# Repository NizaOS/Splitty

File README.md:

<header style="text-align: center; margin-bottom: 40px;">
<h1 style="font-size: 3em; margin-bottom: 10px;">SPLITTY</h1>
<p style="font-size: 1.2em; color: #555;">A 40% Wireless Split Mechanical Keyboard</p>
<p><b>Low Profile &bull; Choc v1 &bull; ZMK Firmware &bull; 1000mAh Battery Life</b></p>
<hr>
</header>
<section>
<h2>Project Overview</h2>
<p>SPLITTY is a custom-built, wireless split keyboard designed for portability and ergonomics. It utilizes the <b>Seeed Studio XIAO nRF52840</b> for Bluetooth 5.0 connectivity and is built on a custom PCB optimized for <b>Kailh Choc v1</b> low-profile switches.</p>

<h3>why i made this project</h3>
    <p>i wanted a low profile split keyboard that was actually portable and didnt cost a fortune. most commerical options are too bulky or wired only so i decided to desin something that fits in a laptop bag easily while keeping the ergonomics of a split layout.</p>

<h3>how to use</h3>
    <p>to use the keyboard you need to flash zmk firmware to both halves. double tap reset button on the xiao to enter bootloader mode then drag and drop the uf2 files. once its flashed you can pair it to your computer via bluetooth settings by searching for splitty. the left side is usually the central half that connects to the pc.</p>
    <h3>Technical Specifications</h3>
    <ul>
        <li><b>Microcontroller:</b> 2x Seeed Studio XIAO nRF52840 (Bluetooth 5.0)</li>
        <li><b>Switch Type:</b> Kailh Choc v1 (PG1350) - Linear/Tactile/Clicky</li>
        <li><b>Battery:</b> 2x 1000mAh LiPo (WLY394058) - Approx. 1+ month battery life</li>
        <li><b>PCB Features:</b> Hotswap support, reversible footprint, 1.2mm thickness</li>
        <li><b>Firmware:</b> ZMK (Wireless-first firmware)</li>
    </ul>
</section>
<hr>
<section>
    <h2>Bill of Materials (BOM)</h2>
    <p><i>Prices estimated in USD based on INR conversion ($1 &#8776; &#8377;90.27).</i></p>
            <table border="1" cellpadding="10" cellspacing="0" style="width: 100%; border-collapse: collapse; text-align: left;">
        <thead>
            <tr style="background-color: #f2f2f2;">
                <th>Component</th>
                <th>Qty</th>
                <th>Unit Price</th>
                <th>Total (USD)</th>
                <th>Sourcing Link</th>
            </tr>
        </thead>
        <tbody>
            <tr>
                <td><b>Seeed XIAO BLE nRF52840</b></td>
                <td>2</td>
                <td>$14.88</td>
                <td>$25.87</td>
                <td><a href="[https://www.fabtolab.com/seeed-xiao-ble-nrf52840-supports-arduino-micropython-bluetooth5.0-onboard-antenna-microcontroller-32-bit-arm-cortex-m4](https://www.fabtolab.com/seeed-xiao-ble-nrf52840-supports-arduino-micropython-bluetooth5.0-onboard-antenna-microcontroller-32-bit-arm-cortex-m4)" target="_blank">Fab.to.Lab</a></td>
            </tr>
            <tr>
                <td><b>Kailh Choc v1 Switches</b></td>
                <td>40</td>
                <td>$0.55</td>
                <td>$22.00</td>
                <td><a href="[https://neomacro.in/products/kailh-choc-pg1350-hot-swap-sockets?srsltid=AfmBOor8u36EImYNmOMVrunXb-IJBcmzE4elqdvKx1VKok2jcNJwbEJO](https://neomacro.in/products/kailh-choc-pg1350-hot-swap-sockets?srsltid=AfmBOor8u36EImYNmOMVrunXb-IJBcmzE4elqdvKx1VKok2jcNJwbEJO)" target="_blank">NeoMacro</a></td>
            </tr>
            <tr>
                <td><b>Choc Hotswap Sockets</b></td>
                <td>40</td>
                <td>$0.18</td>
                <td>$7.00</td>
                <td><a href="[https://neomacro.in/products/kailh-choc-v1-switches](https://neomacro.in/products/kailh-choc-v1-switches)" target="_blank">NeoMacro</a></td>
            </tr>
            <tr>
                <td><b>MBK/MCC Keycaps</b></td>
                <td>40</td>
                <td>$0.40</td>
                <td>$16.00</td>
                <td><a href="[https://neomacro.in/products/chocfox-cfx-choc-blank-keycaps?variant=49467027685654](https://neomacro.in/products/chocfox-cfx-choc-blank-keycaps?variant=49467027685654)" target="_blank">NeoMacro</a></td>
            </tr>
            <tr>
                <td><b>PCB (Manufacturing)</b></td>
                <td>1</td>
                <td>$21.00</td>
                <td>$21.00</td>
                <td><a href="[https://jlcpcb.com/](https://jlcpcb.com/)" target="_blank">JLCPCB</a></td>
            </tr>
            <tr>
                <td><b>3D Printed Case (Shipping)</b></td>
                <td>1</td>
                <td>$10.00</td>
                <td>$10.00</td>
                <td>Printing Legion</td>
            </tr>
            <tr>
                <td><b>LiPo Battery (1000mAh)</b><br><small>Model: WLY394058 (3.9mm thick)</small></td>
                <td>2</td>
                <td>$4.18</td>
                <td>$8.36</td>
                <td><a href="[https://robu.in/product/wly394058-1000mah-3-7v-single-cell-rechargeable-lipo-battery/](https://robu.in/product/wly394058-1000mah-3-7v-single-cell-rechargeable-lipo-battery/)" target="_blank">Robu.in</a></td>
            </tr>
            <tr>
                <td><b>1N4148W Diodes (SOD-123)</b></td>
                <td>40</td>
                <td>$0.006</td>
                <td>$0.24</td>
                <td><a href="[https://robu.in/product/1n4148w-sod-123-1206-diodereel-of-3000/](https://robu.in/product/1n4148w-sod-123-1206-diodereel-of-3000/)" target="_blank">Robu.in</a></td>
            </tr>
            <tr>
                <td><b>806K1 Resistor (0805)</b></td>
                <td>10</td>
                <td>$0.023</td>
                <td>$0.14</td>
                <td><a href="[https://robu.in/product/ac0402fr-07806kl-yageo-62-5mw-thick-film-resistors-50v-](https://robu.in/product/ac0402fr-07806kl-yageo-62-5mw-thick-film-resistors-50v-)±100ppm-℃-±1-806kω-0402-chip-resistor-surface-mount-rohs/" target="_blank">Robu.in</a></td>
            </tr>
            <tr>
                <td><b>2M1 Resistor (0805)</b></td>
                <td>10</td>
                <td>$0.020</td>
                <td>$0.11</td>
                <td><a href="[https://robu.in/product/rc0603fr-0716rl-yageo-smd-chip-resistor-16-ohm-](https://robu.in/product/rc0603fr-0716rl-yageo-smd-chip-resistor-16-ohm-)±-1-100-mw-0603-1608-metric-thick-film-general-purpose/" target="_blank">Robu.in</a></td>
            </tr>
            <tr style="font-weight: bold; background-color: #e6e6e6;">
                <td colspan="3" style="text-align: right;">ESTIMATED TOTAL</td>
                <td colspan="2">$110.72</td>
            </tr>
        </tbody>
    </table>
</section>

<hr>

<div id="gallery" style="padding: 20px; background-color: #f9f9f9; border: 1px solid #ddd; margin-top: 30px;">
    <h2 style="text-align: center;">Project Gallery</h2>
    <div style="text-align: center; margin-bottom: 20px;">
         
</div>

</div>
</div>

</body>
</html>

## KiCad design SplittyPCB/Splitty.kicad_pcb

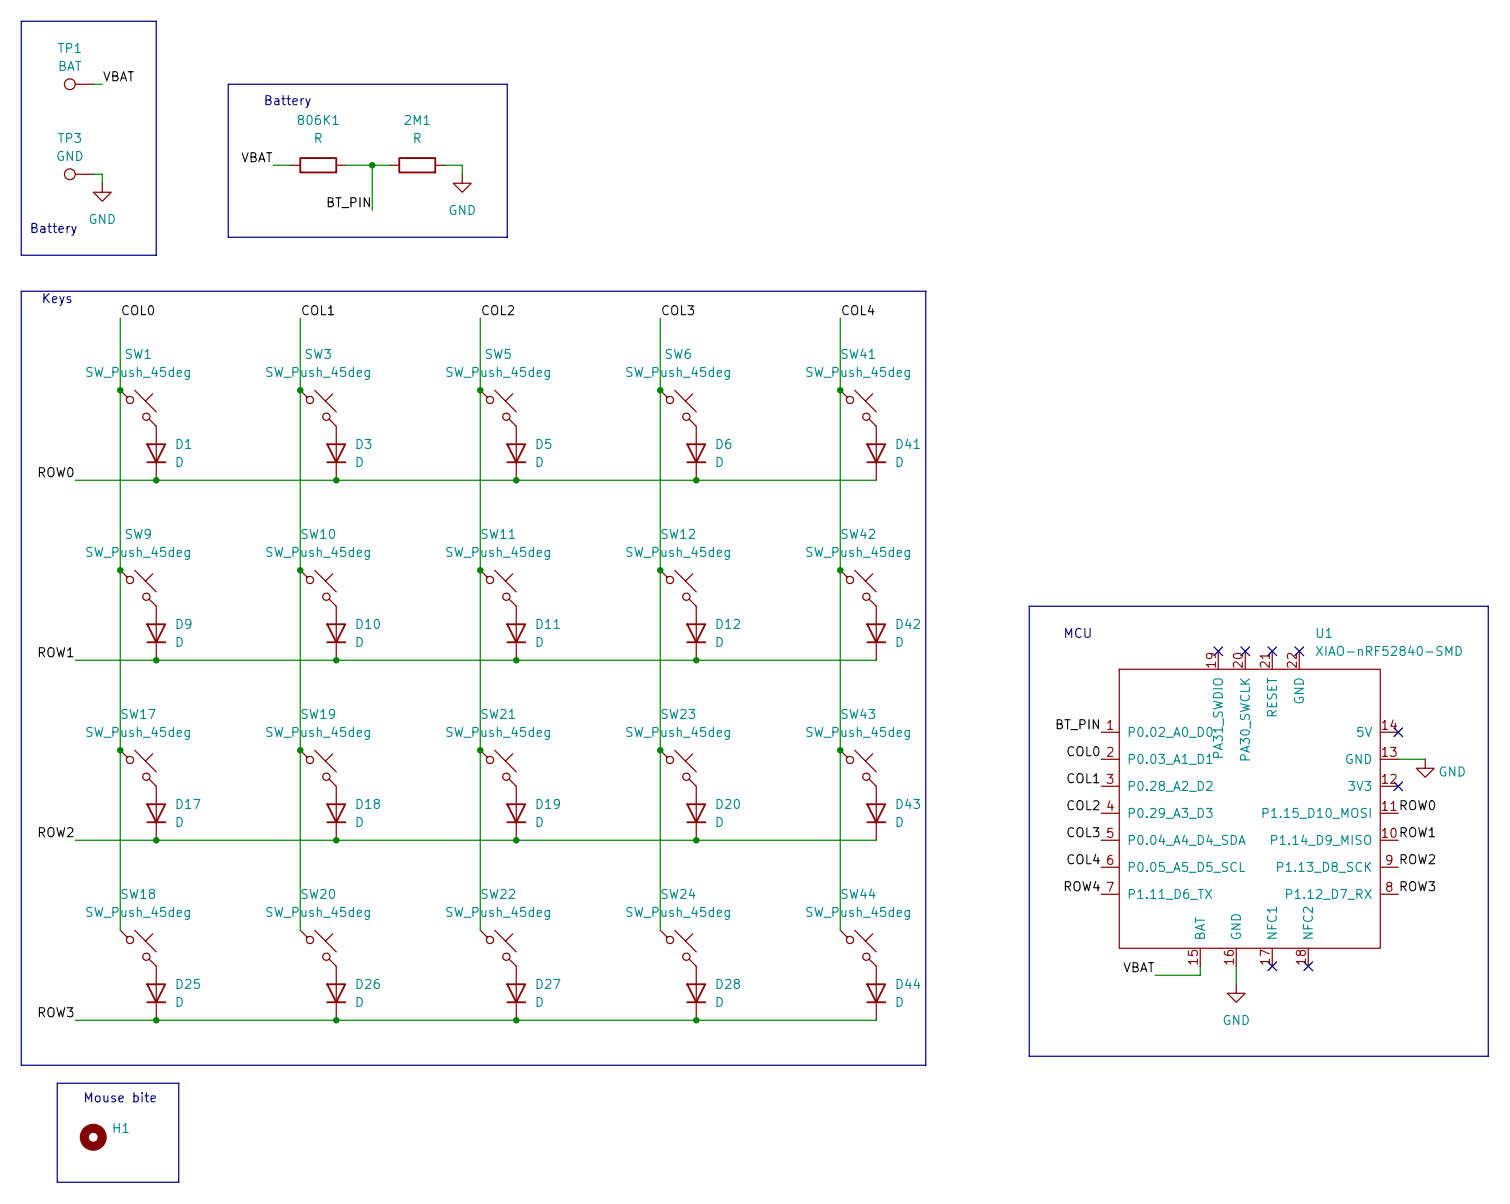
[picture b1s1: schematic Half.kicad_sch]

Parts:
2M1, 806K1: R; R_0805_2012Metric
D1, D3, D5, D6, D9, D10, D11, D12, D17, D18, D19, D20, D25, D26, D27, D28, D41, D42, D43, D44: D; D_SOD-123
H1: MountingHole; mouse-bite-2mm-slot
SW1, SW3, SW5, SW6, SW9, SW10, SW11, SW12, SW17, SW18, SW19, SW20, SW21, SW22, SW23, SW24, SW41, SW42, SW43, SW44: SW_Push_45deg; SW_choc_v1_HS_CPG135001S30_1u
TP1: BAT; TestPoint_Pad_D2.0mm
TP3: GND; TestPoint_Pad_D2.0mm
U1: XIAO-nRF52840-SMD; modified-XIAO-nRF52840-SMD

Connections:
/Left/BT_PIN: 2M1.1, 806K1.2, U1.1 (P0.02_A0_D0)
/Left/COL0: SW1.1, SW9.1, SW17.1, SW18.1, U1.2 (P0.03_A1_D1)
/Left/COL1: SW3.1, SW10.1, SW19.1, SW20.1, U1.3 (P0.28_A2_D2)
/Left/COL2: SW5.1, SW11.1, SW21.1, SW22.1, U1.4 (P0.29_A3_D3)
/Left/COL3: SW6.1, SW12.1, SW23.1, SW24.1, U1.5 (P0.04_A4_D4_SDA)
/Left/COL4: SW41.1, SW42.1, SW43.1, SW44.1, U1.6 (P0.05_A5_D5_SCL)
/Left/ROW0: D1.1 (K), D3.1 (K), D5.1 (K), D6.1 (K), D41.1 (K), U1.11 (P1.15_D10_MOSI)
/Left/ROW1: D9.1 (K), D10.1 (K), D11.1 (K), D12.1 (K), D42.1 (K), U1.10 (P1.14_D9_MISO)
/Left/ROW2: D17.1 (K), D18.1 (K), D19.1 (K), D20.1 (K), D43.1 (K), U1.9 (P1.13_D8_SCK)
/Left/ROW3: D25.1 (K), D26.1 (K), D27.1 (K), D28.1 (K), D44.1 (K), U1.8 (P1.12_D7_RX)
/Left/ROW4: U1.7 (P1.11_D6_TX)
/Left/VBAT: 806K1.1, TP1.1, U1.15 (BAT)
GND: 2M1.2, TP3.1, U1.13 (GND), U1.16 (GND); also elsewhere on the board
unnamed: D1.2 (A), SW1.2
unnamed: D3.2 (A), SW3.2
unnamed: D5.2 (A), SW5.2
unnamed: D6.2 (A), SW6.2
unnamed: D9.2 (A), SW9.2
unnamed: D10.2 (A), SW10.2
unnamed: D11.2 (A), SW11.2
unnamed: D12.2 (A), SW12.2
unnamed: D17.2 (A), SW17.2
unnamed: D18.2 (A), SW19.2
unnamed: D19.2 (A), SW21.2
unnamed: D20.2 (A), SW23.2
unnamed: D25.2 (A), SW18.2
unnamed: D26.2 (A), SW20.2
unnamed: D27.2 (A), SW22.2
unnamed: D28.2 (A), SW24.2
unnamed: D41.2 (A), SW41.2
unnamed: D42.2 (A), SW42.2
unnamed: D43.2 (A), SW43.2
unnamed: D44.2 (A), SW44.2

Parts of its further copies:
D2, D4, D7, D8, D13, D14, D15, D16, D21, D22, D23, D24, D29, D30, D31, D32, D46, D47, D48, D49: D; D_SOD-123
R2, R4: R; R_0805_2012Metric
SW2, SW4, SW7, SW8, SW13, SW14, SW15, SW16, SW25, SW26, SW27, SW28, SW29, SW30, SW31, SW32, SW46, SW47, SW48, SW49: SW_Push_45deg; SW_choc_v1_HS_CPG135001S30_1u
TP2: BAT; TestPoint_Pad_D2.0mm
TP4: GND; TestPoint_Pad_D2.0mm
U2: XIAO-nRF52840-SMD; modified-XIAO-nRF52840-SMD

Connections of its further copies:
/Right/BT_PIN: R2.2, R4.1, U2.1 (P0.02_A0_D0)
/Right/COL0: SW2.1, SW13.1, SW25.1, SW26.1, U2.2 (P0.03_A1_D1)
/Right/COL1: SW4.1, SW14.1, SW27.1, SW28.1, U2.3 (P0.28_A2_D2)
/Right/COL2: SW7.1, SW15.1, SW29.1, SW30.1, U2.4 (P0.29_A3_D3)
/Right/COL3: SW8.1, SW16.1, SW31.1, SW32.1, U2.5 (P0.04_A4_D4_SDA)
/Right/COL4: SW46.1, SW47.1, SW48.1, SW49.1, U2.6 (P0.05_A5_D5_SCL)
/Right/ROW0: D2.1 (K), D4.1 (K), D7.1 (K), D8.1 (K), D46.1 (K), U2.11 (P1.15_D10_MOSI)
/Right/ROW1: D13.1 (K), D14.1 (K), D15.1 (K), D16.1 (K), D47.1 (K), U2.10 (P1.14_D9_MISO)
/Right/ROW2: D21.1 (K), D22.1 (K), D23.1 (K), D24.1 (K), D48.1 (K), U2.9 (P1.13_D8_SCK)
/Right/ROW3: D29.1 (K), D30.1 (K), D31.1 (K), D32.1 (K), D49.1 (K), U2.8 (P1.12_D7_RX)
/Right/ROW4: U2.7 (P1.11_D6_TX)
/Right/VBAT: R2.1, TP2.1, U2.15 (BAT)
GND: R4.2, TP4.1, U2.13 (GND), U2.16 (GND); also elsewhere on the board
unnamed: D2.2 (A), SW2.2
unnamed: D4.2 (A), SW4.2
unnamed: D7.2 (A), SW7.2
unnamed: D8.2 (A), SW8.2
unnamed: D13.2 (A), SW13.2
unnamed: D14.2 (A), SW14.2
unnamed: D15.2 (A), SW15.2
unnamed: D16.2 (A), SW16.2
unnamed: D21.2 (A), SW25.2
unnamed: D22.2 (A), SW27.2
unnamed: D23.2 (A), SW29.2
unnamed: D24.2 (A), SW31.2
unnamed: D29.2 (A), SW26.2
unnamed: D30.2 (A), SW28.2
unnamed: D31.2 (A), SW30.2
unnamed: D32.2 (A), SW32.2
unnamed: D46.2 (A), SW46.2
unnamed: D47.2 (A), SW47.2
unnamed: D48.2 (A), SW48.2
unnamed: D49.2 (A), SW49.2

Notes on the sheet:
Keys
Battery
Mouse bite
Battery
MCU

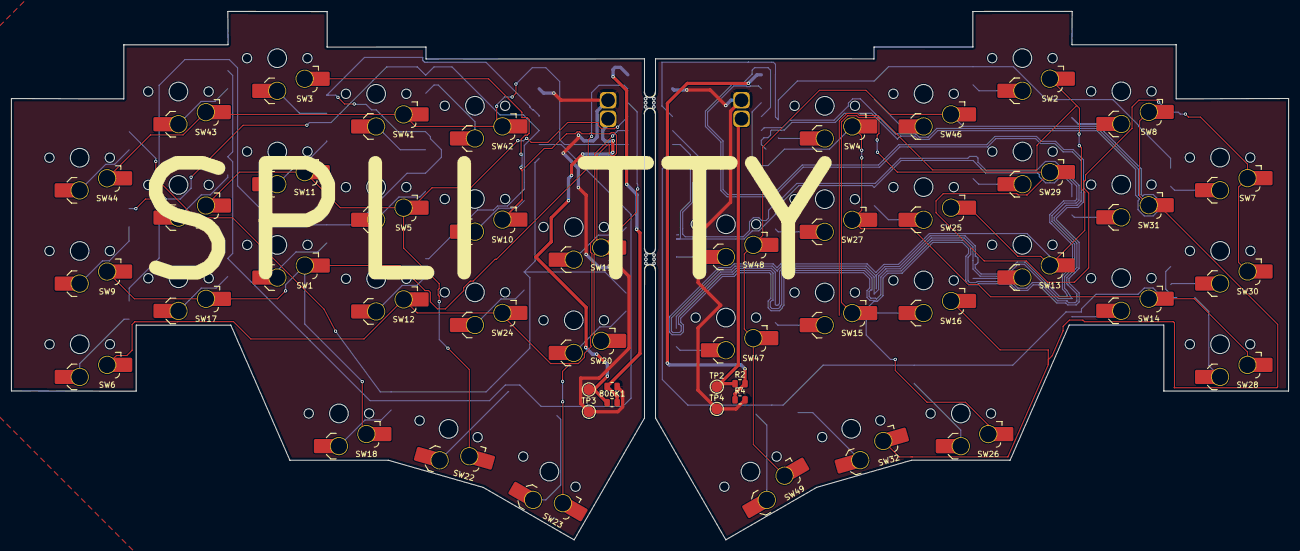
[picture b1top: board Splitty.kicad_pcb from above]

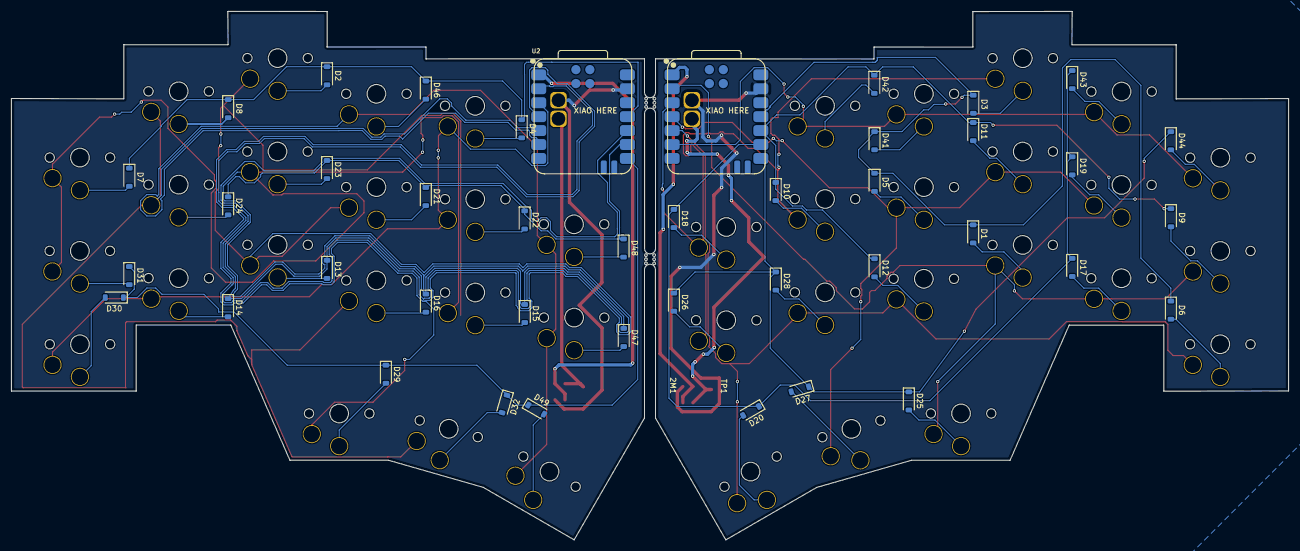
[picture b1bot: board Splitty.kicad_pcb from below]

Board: 2 copper layers, 232.7 x 96.3 mm, 92 parts (42 on the bottom side), 63 nets.

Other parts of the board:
H2, H4: break off; mouse-bite-2mm-slot

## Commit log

2026-01-09 Added PCB designs
2026-01-09 Added CAD files
2026-01-10 move
2026-01-20 added cad model with all components included and unified parts
2026-01-22 added splittyfull file
2026-01-31 Added BOM file
2026-01-31 Rename SBOM.csv to BOM.csv
2026-03-31 The firmware
